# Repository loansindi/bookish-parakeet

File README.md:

# What is it?
The goal here is to build a small, short-duty-cycle blinking device that's easy to power for at least a day or two at a time.

Design is in extremely early stages.

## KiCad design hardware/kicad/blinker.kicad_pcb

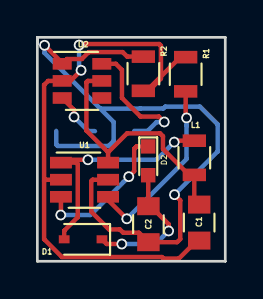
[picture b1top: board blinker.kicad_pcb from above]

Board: 2 copper layers, 10.4 x 12.4 mm, 9 parts (0 on the bottom side), 7 nets.

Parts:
C1, C2: 4.7uF; C_0805
D1: D_Schottky; D_SOD-323
D2: LED; LED_0603
L1: 4.7uH; L_0805
R1, R2: 4.53K; R_0805
U1: LT1932ES6; TSOT-23-6
U2: ATTINY10; SOT-23-6

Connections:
GND: C1.2, R1.2, R2.2, U1.2, U2.2
unnamed: C2.1, D1.1, D2.2
unnamed: C2.2, R2.1, U1.5, U2.1
unnamed: D1.2, L1.1, U1.1
unnamed: D2.1, U1.3
unnamed: R1.1, U1.4
VCC: C1.1, L1.2, U1.6, U2.5

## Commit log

2018-05-15 Hardware files
2018-05-15 Sketch out repo
2018-05-15 I know how to markdown.
2018-05-15 add shared cart link
2018-05-31 new PCB
2018-05-31 add code
2018-06-02 add kicad board design
